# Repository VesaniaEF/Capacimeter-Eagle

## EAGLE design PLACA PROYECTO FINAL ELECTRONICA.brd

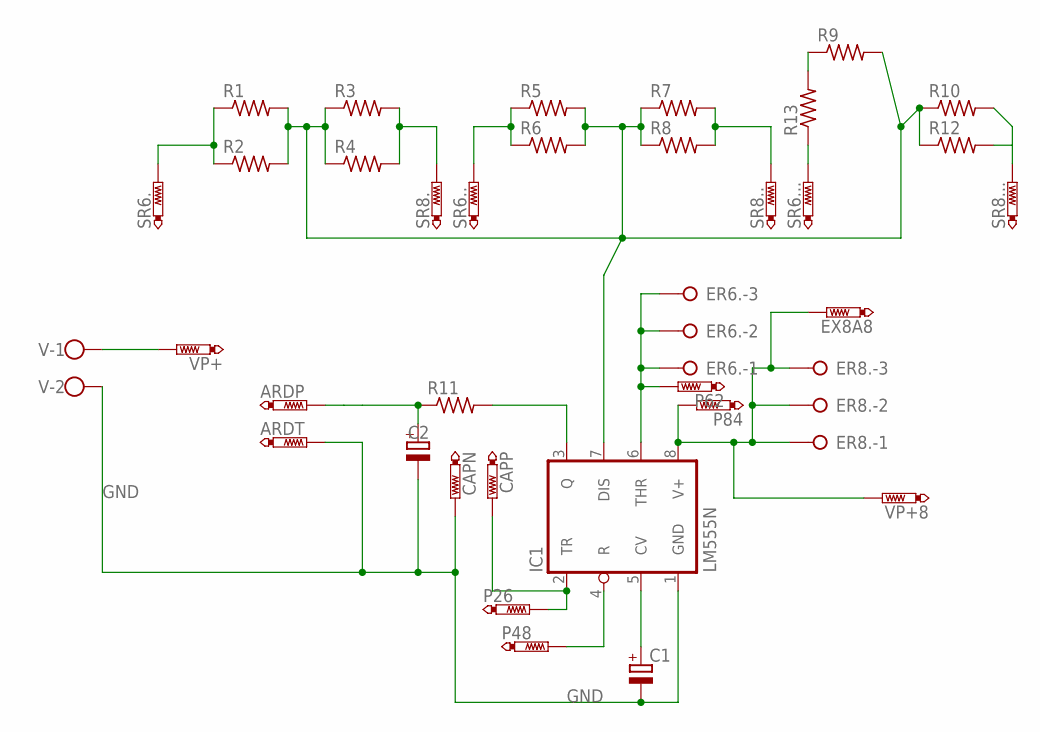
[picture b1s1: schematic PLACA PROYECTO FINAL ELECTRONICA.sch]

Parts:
ARDP: PTR1PAD1-17; P1-17
ARDT: PTR1PAD1-13; P1-13
C1, C2: CPOL-EUE2,5-6E; E2,5-6E
CAPN: PTR1PAD1-17; P1-17
CAPP: PTR1PAD1-17; P1-17
ER6., ER8.: W237-3E
EX8A8: PTR1PAD1-13; P1-13
IC1: LM555N; DIL08
P26, P48, P62, P84: PTR1PAD1-17; P1-17
R1, R2, R3, R4, R5, R6, R7, R8, R9, R10, R11, R12, R13: R-US_0204/7; 0204/7
SR6., SR6.., SR6..., SR8., SR8.., SR8...: PTR1PAD1-13; P1-13
V: W237-102
VP+, VP+8: PTR1PAD1-13; P1-13

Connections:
GND: ARDT.TP, C1.-, C2.-, CAPN.TP, IC1.1 (GND), V.2
unnamed: R10.2, R12.2, SR8....TP
unnamed: R1.1, R2.1, SR6..TP
unnamed: ER6..1, ER6..2, ER6..3, IC1.6 (THR), P62.TP
unnamed: R5.1, R6.1, SR6...TP
unnamed: ER8..1, ER8..2, ER8..3, EX8A8.TP, IC1.8 (V+), P84.TP, VP+8.TP
unnamed: R9.1, R13.2
unnamed: IC1.3 (Q), R11.2
unnamed: CAPP.TP, IC1.2 (TR), P26.TP
unnamed: ARDP.TP, C2.+, R11.1
unnamed: C1.+, IC1.5 (CV)
unnamed: V.1, VP+.TP
unnamed: IC1.7 (DIS), R1.2, R2.2, R3.1, R4.1, R5.2, R6.2, R7.1, R8.1, R9.2, R10.1, R12.1
unnamed: IC1.4 (R), P48.TP
unnamed: R3.2, R4.2, SR8..TP
unnamed: R7.2, R8.2, SR8...TP
unnamed: R13.1, SR6....TP

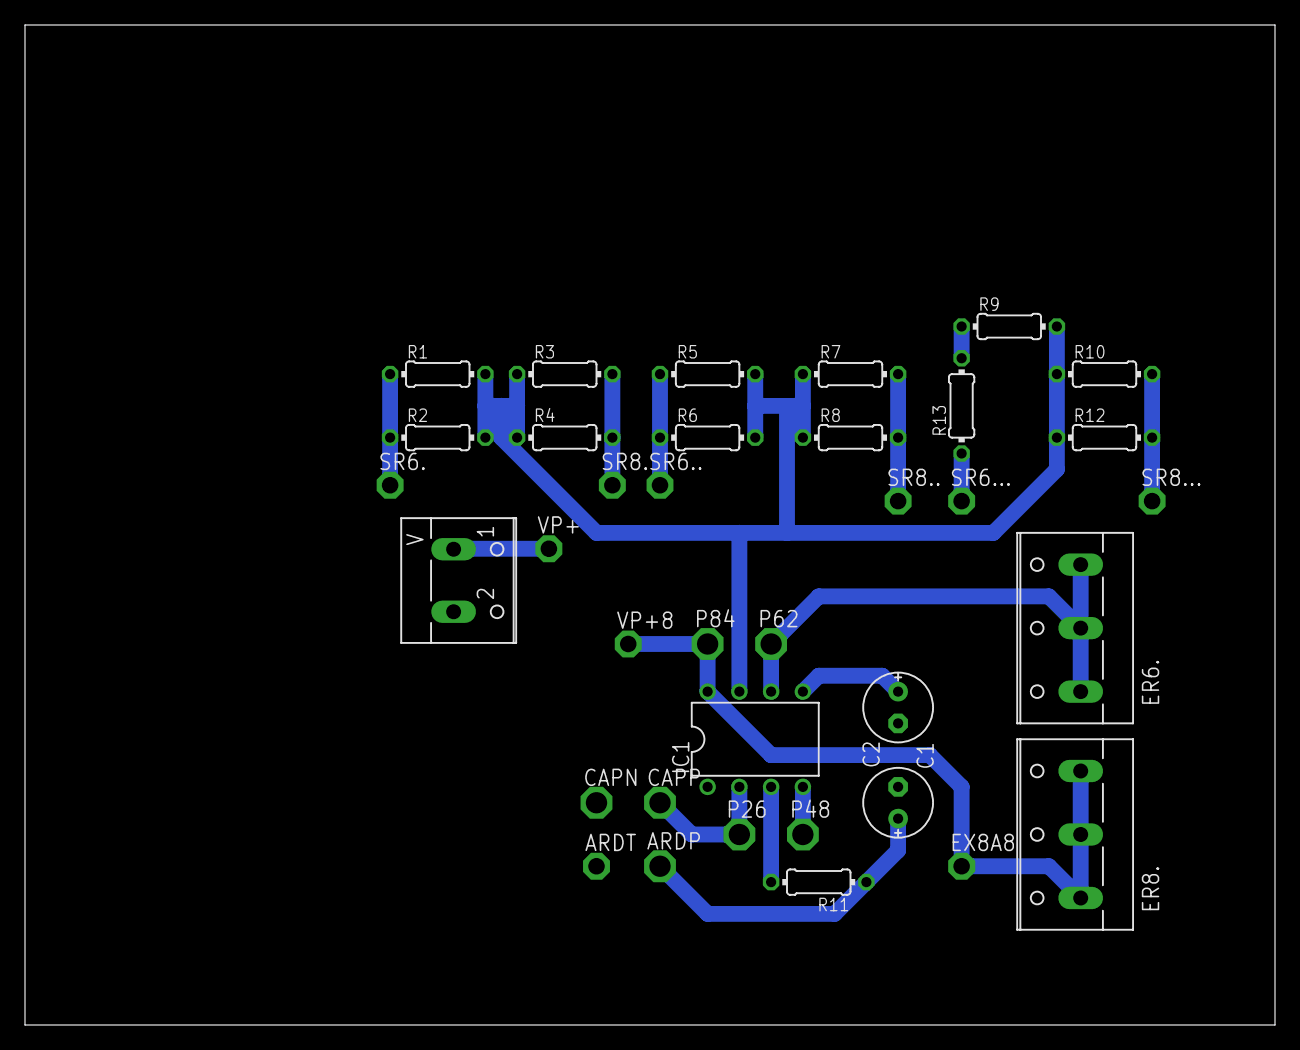
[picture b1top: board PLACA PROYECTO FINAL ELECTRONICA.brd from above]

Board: 2 copper layers, 100.0 x 80.0 mm, 36 parts (0 on the bottom side), 17 nets.
